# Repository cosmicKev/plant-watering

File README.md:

# Self Watering Plant

To keep your veggies alive that came alive from the [OfferZen] (http://offerzen.com/nl/make) workshop

# Features
  - ESP32 (Wifi / Bluetooth)
  - Flashing is done with a single USB-TypeC
  - Power in:
    - USB at 5V @ 2A max
  - Outputs
    - 2x waterpumps individually with shared power supply of either +5V or +12V
    - 2x USB 5V led strips individually controlled.
  - Sensors:
    - 2x external moisture sensors
    - 1x on board light sensor
    - 1x on board humidity & temperature sesor
    - 1x user custom sensor (till 3.3V

# MCAD - Mechanical CAD
## Pot pipe clips

## Electronics Enclosure

# ECAD - Electronics CAD

# Firmware

# Version

# Authors
Kevin Pinto

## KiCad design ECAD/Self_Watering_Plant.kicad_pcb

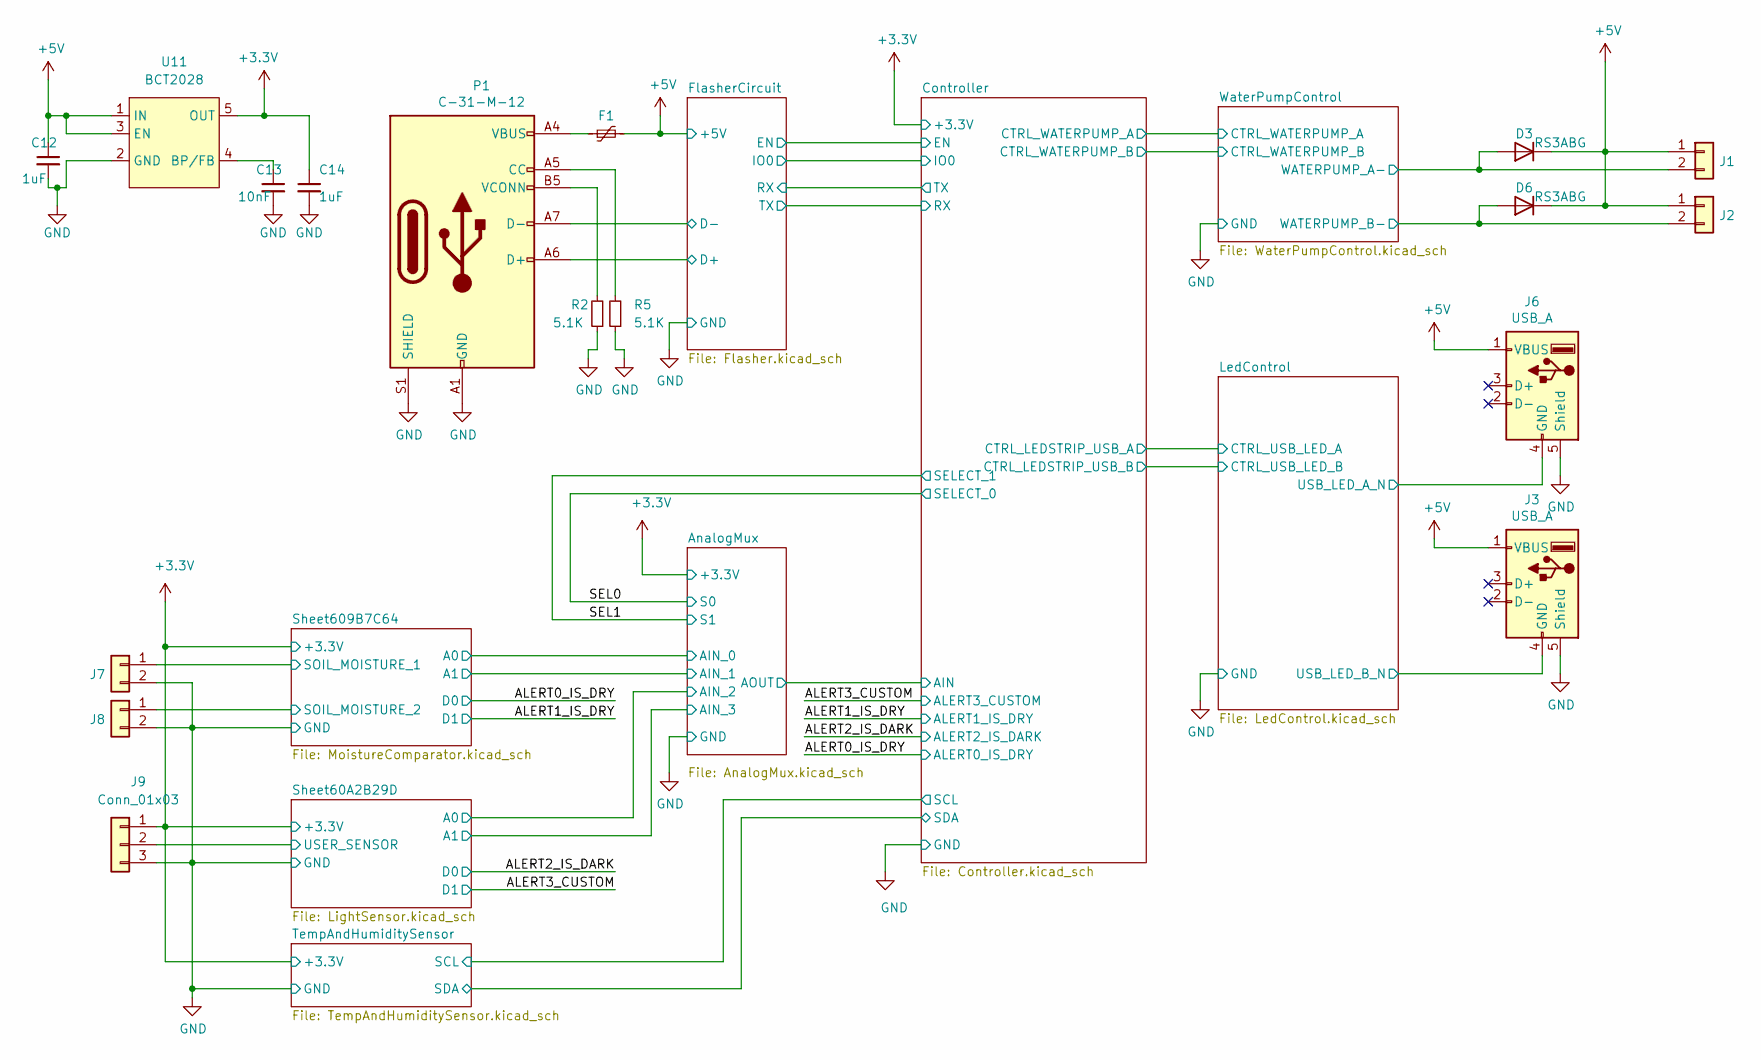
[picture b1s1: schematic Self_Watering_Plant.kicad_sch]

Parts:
C12, C14: 1uF; C_0603_1608Metric
C13: 10nF; C_0603_1608Metric
D3, D6: RS3ABG; D_SMB
F1: Polyfuse_Small; Fuse_1812_4532Metric
J1, J2: Conn_01x02; TB001-500-02BE
J3, J6: USB_A; USB_A_Molex_67643_Horizontal
J7, J8: Conn_01x02; JST_XH_S2B-XH-A_1x02_P2.50mm_Horizontal
J9: Conn_01x03; JST_XH_S3B-XH-A_1x03_P2.50mm_Horizontal
P1: C-31-M-12; USB_C_Receptacle_HRO_TYPE-C-31-M-12
R2, R5: 5.1K; R_0603_1608Metric
U11: BCT2028; SOT-23-5

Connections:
+3V3: C14.1, J9.1, U11.5 (OUT); also elsewhere on the board
+5V: C12.1, D3.1 (K), D6.1 (K), F1.2, J1.1, J2.1, J3.1 (VBUS), J6.1 (VBUS), U11.1 (IN), U11.3 (EN); also elsewhere on the board
/AnalogMux/AIN_0: J8.1; also elsewhere on the board
/AnalogMux/AIN_1: J7.1; also elsewhere on the board
/AnalogMux/AIN_2: J9.2; also elsewhere on the board
/FlasherCircuit/D+: P1.A6 (D+); also elsewhere on the board
/FlasherCircuit/D-: P1.A7 (D-); also elsewhere on the board
/LedControl/USB_LED_A_N: J6.4 (GND); also elsewhere on the board
/LedControl/USB_LED_B_N: J3.4 (GND); also elsewhere on the board
/WaterPumpControl/WATERPUMP_A-: D3.2 (A), J1.2; also elsewhere on the board
/WaterPumpControl/WATERPUMP_B-: D6.2 (A), J2.2; also elsewhere on the board
GND: C12.2, C13.2, C14.2, J3.5 (Shield), J6.5 (Shield), J7.2, J8.2, J9.3, P1.A1 (GND), P1.A12 (GND), P1.B1 (GND), P1.B12 (GND), P1.S1 (SHIELD), R2.1, R5.1, U11.2 (GND); also elsewhere on the board
unnamed: C13.1, U11.4 (BP/FB)
unnamed: F1.1, P1.A4 (VBUS), P1.A9 (VBUS), P1.B4 (VBUS), P1.B9 (VBUS)
unnamed: P1.A5 (CC), R5.2
unnamed: P1.B5 (VCONN), R2.2

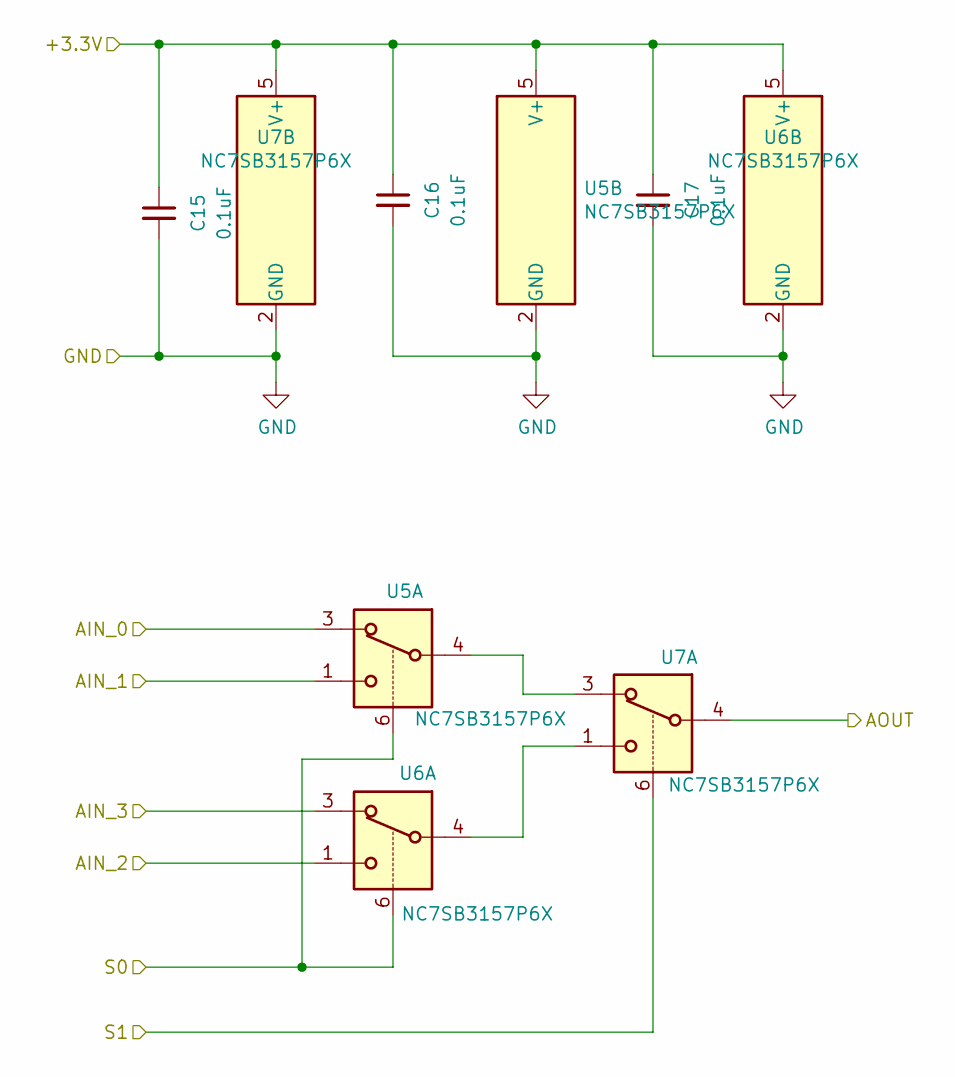
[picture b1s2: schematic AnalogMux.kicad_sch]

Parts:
C15, C16, C17: 0.1uF; C_0603_1608Metric
U5, U6, U7: NC7SB3157P6X; SOT-363_SC-70-6

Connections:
+3V3: C15.1, C16.1, C17.1, U5.5 (V+), U6.5 (V+), U7.5 (V+); also elsewhere on the board
/AnalogMux/AIN_0: U5.3; also elsewhere on the board
/AnalogMux/AIN_1: U5.1; also elsewhere on the board
/AnalogMux/AIN_2: U6.1; also elsewhere on the board
/AnalogMux/AIN_3: U6.3; also elsewhere on the board
/AnalogMux/AOUT: U7.4; also elsewhere on the board
/SEL0: U5.6, U6.6; also elsewhere on the board
/SEL1: U7.6; also elsewhere on the board
GND: C15.2, C16.2, C17.2, U5.2 (GND), U6.2 (GND), U7.2 (GND); also elsewhere on the board
unnamed: U5.4, U7.3
unnamed: U6.4, U7.1

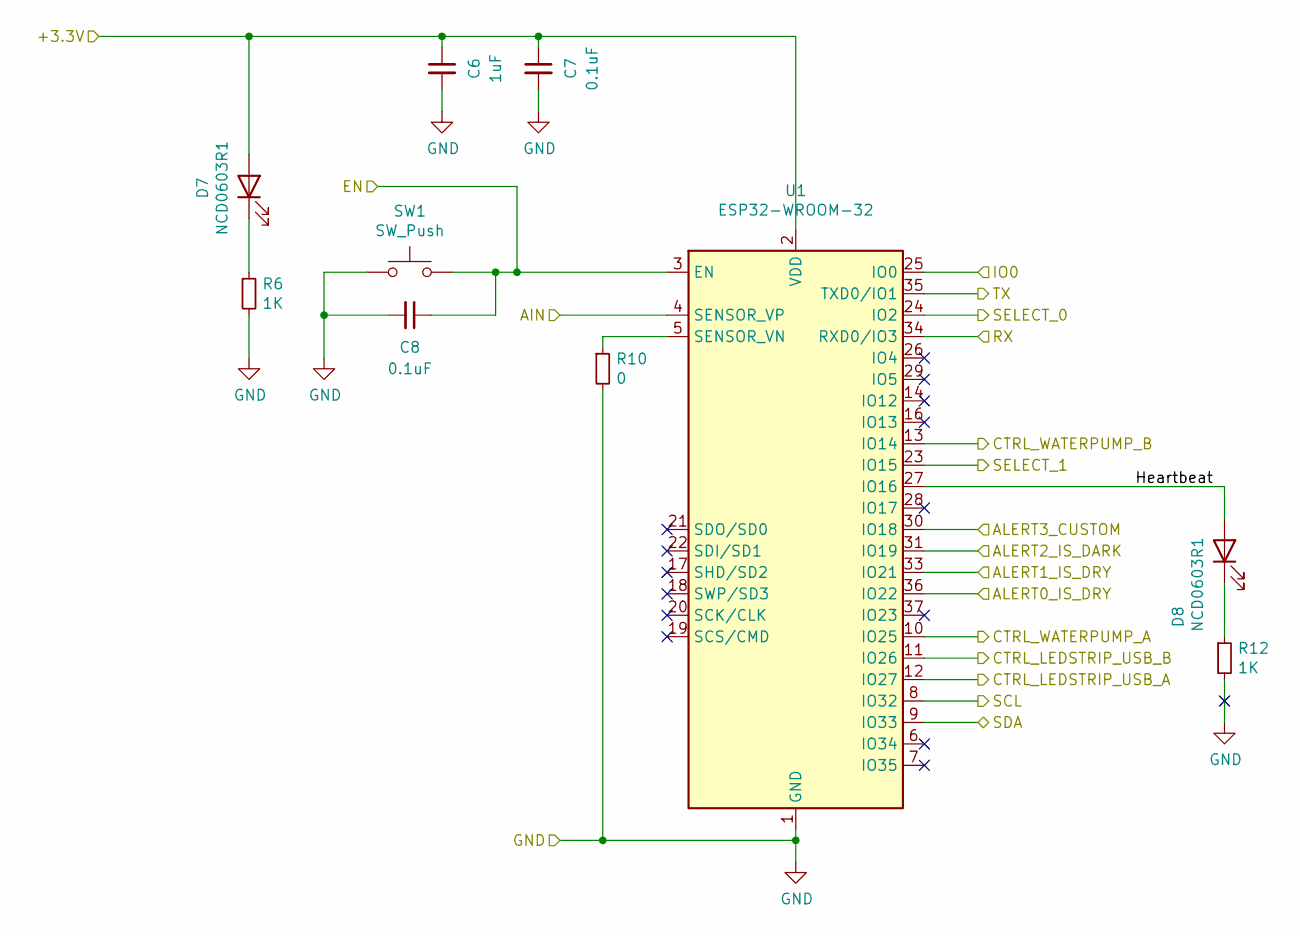
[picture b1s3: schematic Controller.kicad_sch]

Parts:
C6: 1uF; C_0603_1608Metric
C7, C8: 0.1uF; C_0603_1608Metric
D7, D8: NCD0603R1; LED_0603_1608Metric
R6, R12: 1K; R_0603_1608Metric
R10: 0; R_0603_1608Metric
SW1: SW_Push; SW_PUSH_6mm_H4.3mm
U1: ESP32-WROOM-32

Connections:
+3V3: C6.1, C7.1, D7.2 (A), U1.2 (VDD); also elsewhere on the board
/ALERT0_IS_DRY: U1.36 (IO22); also elsewhere on the board
/ALERT1_IS_DRY: U1.33 (IO21); also elsewhere on the board
/ALERT2_IS_DARK: U1.31 (IO19); also elsewhere on the board
/ALERT3_CUSTOM: U1.30 (IO18); also elsewhere on the board
/AnalogMux/AOUT: U1.4 (SENSOR_VP); also elsewhere on the board
/Controller/CTRL_LEDSTRIP_USB_A: U1.12 (IO27); also elsewhere on the board
/Controller/CTRL_LEDSTRIP_USB_B: U1.11 (IO26); also elsewhere on the board
/Controller/CTRL_WATERPUMP_A: U1.10 (IO25); also elsewhere on the board
/Controller/CTRL_WATERPUMP_B: U1.13 (IO14); also elsewhere on the board
/Controller/EN: C8.1, SW1.2, U1.3 (EN); also elsewhere on the board
/Controller/Heartbeat: D8.2 (A), U1.27 (IO16)
/Controller/IO0: U1.25 (IO0); also elsewhere on the board
/Controller/RX: U1.34 (RXD0/IO3); also elsewhere on the board
/Controller/SCL: U1.8 (IO32); also elsewhere on the board
/Controller/SDA: U1.9 (IO33); also elsewhere on the board
/Controller/TX: U1.35 (TXD0/IO1); also elsewhere on the board
/SEL0: U1.24 (IO2); also elsewhere on the board
/SEL1: U1.23 (IO15); also elsewhere on the board
GND: C6.2, C7.2, C8.2, R6.2, R10.2, R12.2, SW1.1, U1.1 (GND), U1.15 (GND), U1.38 (GND), U1.39 (GND); also elsewhere on the board
unnamed: D7.1 (K), R6.1
unnamed: D8.1 (K), R12.1
unnamed: R10.1, U1.5 (SENSOR_VN)

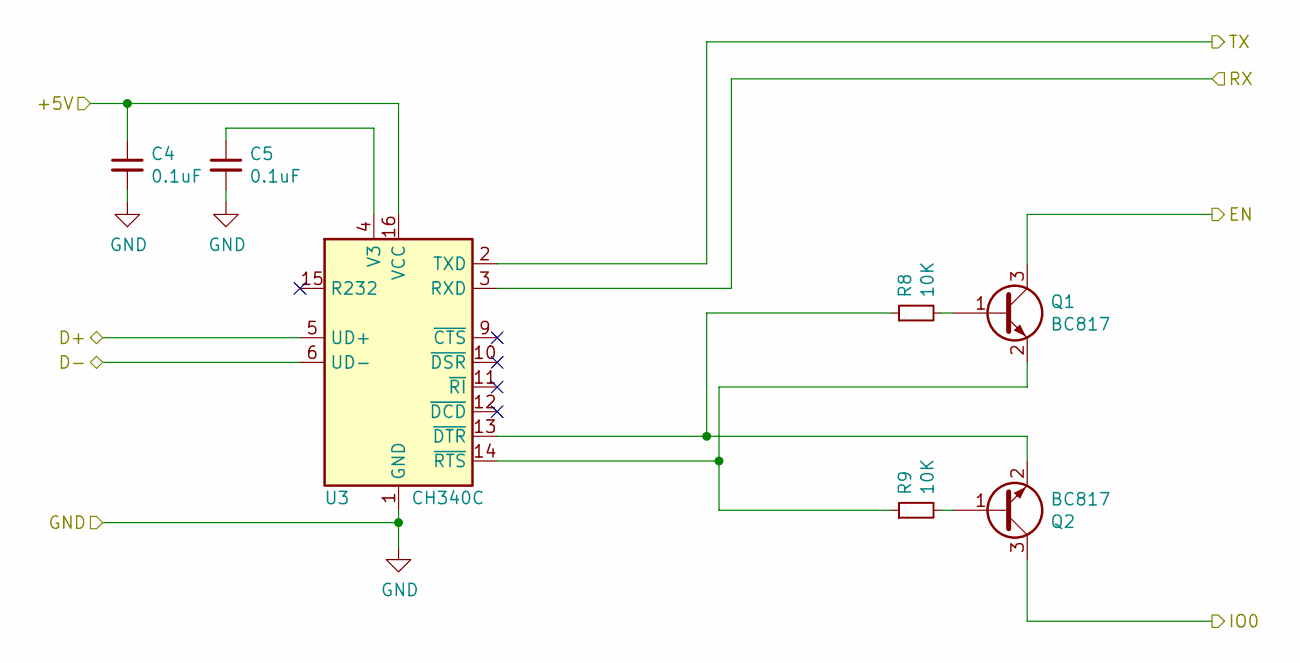
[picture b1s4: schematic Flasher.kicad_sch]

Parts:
C4, C5: 0.1uF; C_0603_1608Metric
Q1, Q2: BC817; SOT-23
R8, R9: 10K; R_0603_1608Metric
U3: CH340C; SOIC-16_3.9x9.9mm_P1.27mm

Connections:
+5V: C4.1, U3.16 (VCC); also elsewhere on the board
/Controller/EN: Q1.3 (C); also elsewhere on the board
/Controller/IO0: Q2.3 (C); also elsewhere on the board
/Controller/RX: U3.2 (TXD); also elsewhere on the board
/Controller/TX: U3.3 (RXD); also elsewhere on the board
/FlasherCircuit/D+: U3.5 (UD+); also elsewhere on the board
/FlasherCircuit/D-: U3.6 (UD-); also elsewhere on the board
GND: C4.2, C5.2, U3.1 (GND); also elsewhere on the board
unnamed: C5.1, U3.4 (V3)
unnamed: Q1.1 (B), R8.2
unnamed: Q1.2 (E), R9.1, U3.14 (~RTS)
unnamed: Q2.1 (B), R9.2
unnamed: Q2.2 (E), R8.1, U3.13 (~DTR)

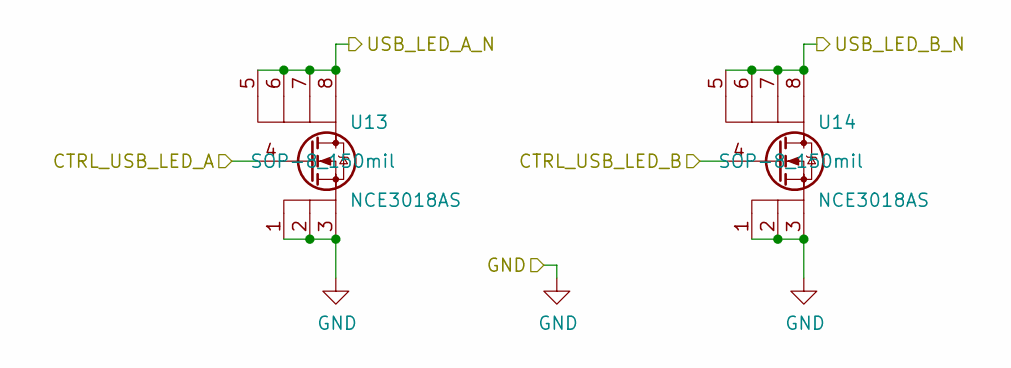
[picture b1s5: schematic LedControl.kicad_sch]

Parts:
U13, U14: NCE3018AS; SO-8_3.9x4.9mm_P1.27mm

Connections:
/Controller/CTRL_LEDSTRIP_USB_A: U13.4; also elsewhere on the board
/Controller/CTRL_LEDSTRIP_USB_B: U14.4; also elsewhere on the board
/LedControl/USB_LED_A_N: U13.5, U13.6, U13.7, U13.8; also elsewhere on the board
/LedControl/USB_LED_B_N: U14.5, U14.6, U14.7, U14.8; also elsewhere on the board
GND: U13.1, U13.2, U13.3, U14.1, U14.2, U14.3; also elsewhere on the board

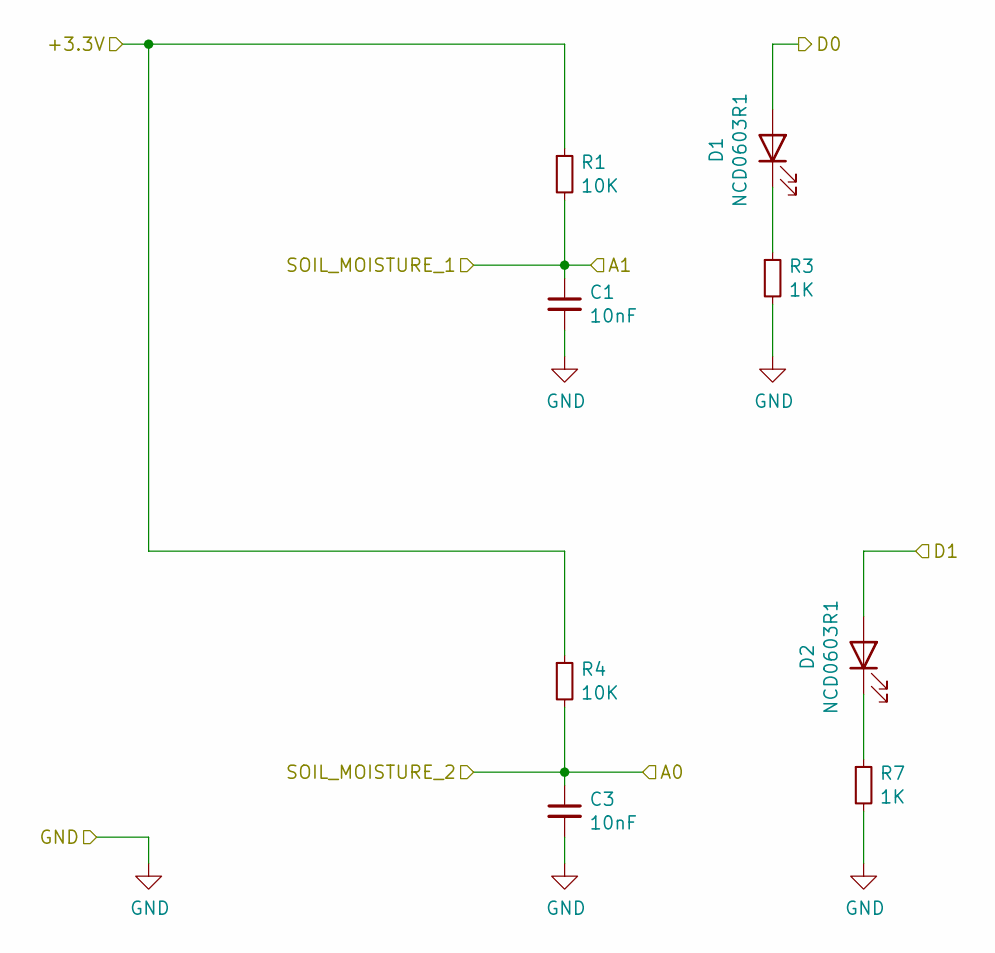
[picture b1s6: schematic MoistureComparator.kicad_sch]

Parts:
C1, C3: 10nF; C_0603_1608Metric
D1, D2: NCD0603R1; LED_0603_1608Metric
R1, R4: 10K; R_0603_1608Metric
R3, R7: 1K; R_0603_1608Metric

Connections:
+3V3: R1.1, R4.1; also elsewhere on the board
/ALERT0_IS_DRY: D1.2 (A); also elsewhere on the board
/ALERT1_IS_DRY: D2.2 (A); also elsewhere on the board
/AnalogMux/AIN_0: C3.1, R4.2; also elsewhere on the board
/AnalogMux/AIN_1: C1.1, R1.2; also elsewhere on the board
GND: C1.2, C3.2, R3.2, R7.2; also elsewhere on the board
unnamed: D1.1 (K), R3.1
unnamed: D2.1 (K), R7.1

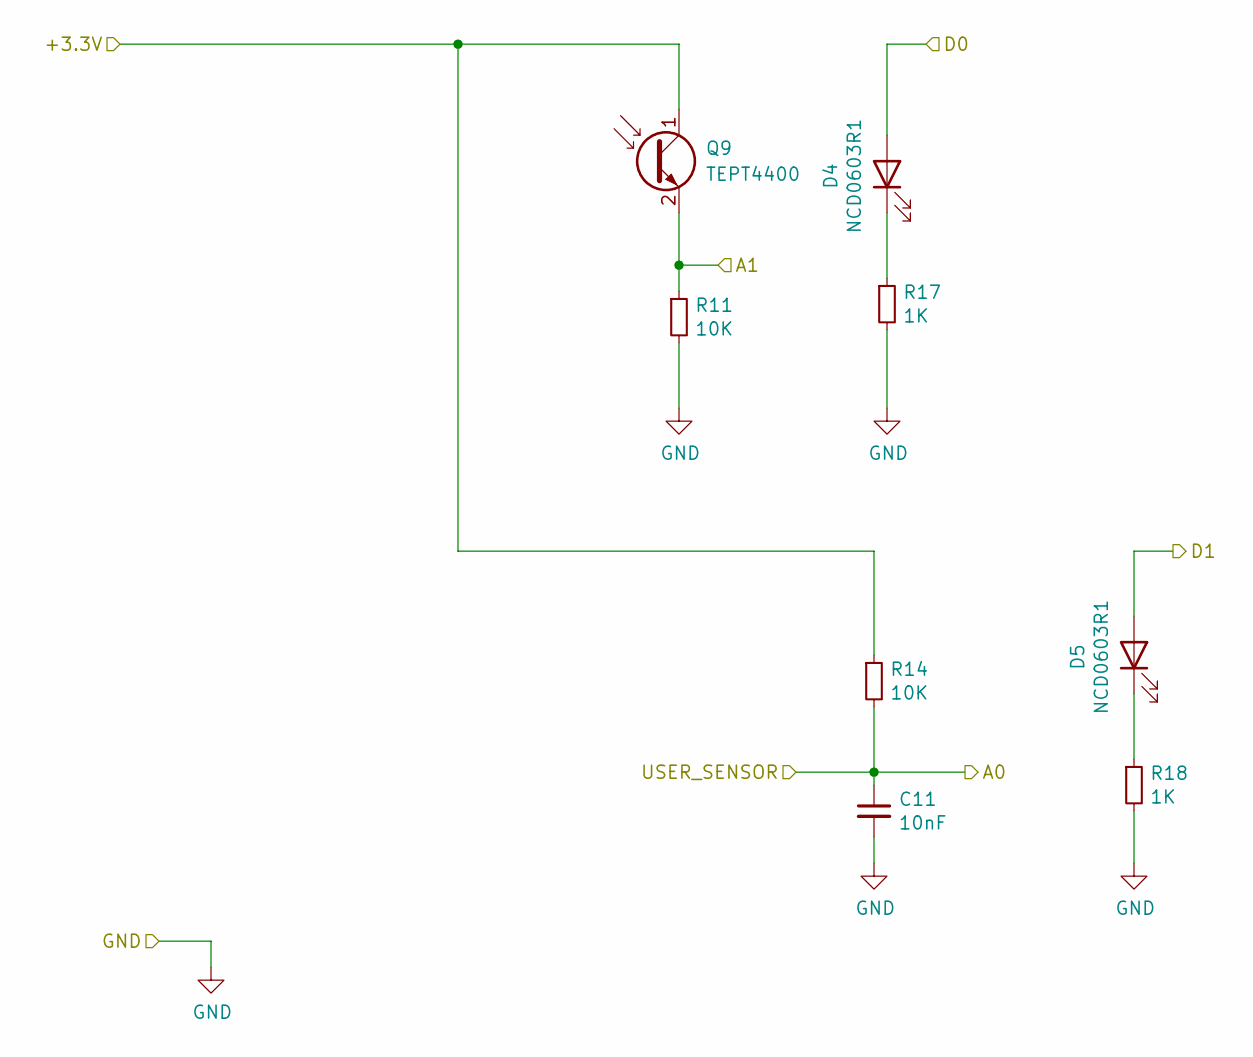
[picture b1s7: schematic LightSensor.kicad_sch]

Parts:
C11: 10nF; C_0603_1608Metric
D4, D5: NCD0603R1; LED_0603_1608Metric
Q9: TEPT4400; LED_D3.0mm_Clear
R11, R14: 10K; R_0603_1608Metric
R17, R18: 1K; R_0603_1608Metric

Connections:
+3V3: Q9.1 (C), R14.1; also elsewhere on the board
/ALERT2_IS_DARK: D4.2 (A); also elsewhere on the board
/ALERT3_CUSTOM: D5.2 (A); also elsewhere on the board
/AnalogMux/AIN_2: C11.1, R14.2; also elsewhere on the board
/AnalogMux/AIN_3: Q9.2 (E), R11.1; also elsewhere on the board
GND: C11.2, R11.2, R17.2, R18.2; also elsewhere on the board
unnamed: D4.1 (K), R17.1
unnamed: D5.1 (K), R18.1

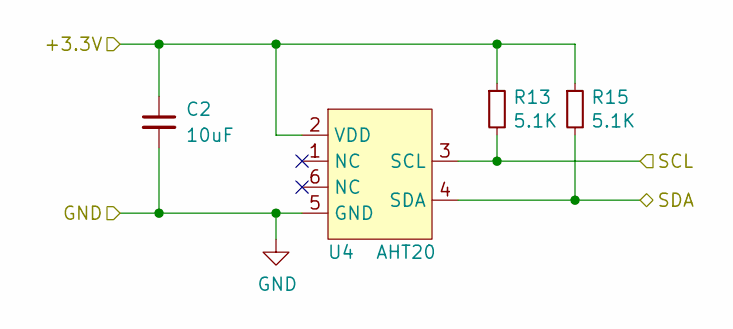
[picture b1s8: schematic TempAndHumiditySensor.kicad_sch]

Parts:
C2: 10uF; C_0603_1608Metric
R13, R15: 5.1K; R_0603_1608Metric
U4: AHT20; SOIC-6

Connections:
+3V3: C2.1, R13.1, R15.1, U4.2 (VDD); also elsewhere on the board
/Controller/SCL: R13.2, U4.3 (SCL); also elsewhere on the board
/Controller/SDA: R15.2, U4.4 (SDA); also elsewhere on the board
GND: C2.2, U4.5 (GND); also elsewhere on the board

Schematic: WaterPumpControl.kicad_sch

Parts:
U2, U9: NCE3018AS; SO-8_3.9x4.9mm_P1.27mm

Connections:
/Controller/CTRL_WATERPUMP_A: U2.4; also elsewhere on the board
/Controller/CTRL_WATERPUMP_B: U9.4; also elsewhere on the board
/WaterPumpControl/WATERPUMP_A-: U2.5, U2.6, U2.7, U2.8; also elsewhere on the board
/WaterPumpControl/WATERPUMP_B-: U9.5, U9.6, U9.7, U9.8; also elsewhere on the board
GND: U2.1, U2.2, U2.3, U9.1, U9.2, U9.3; also elsewhere on the board

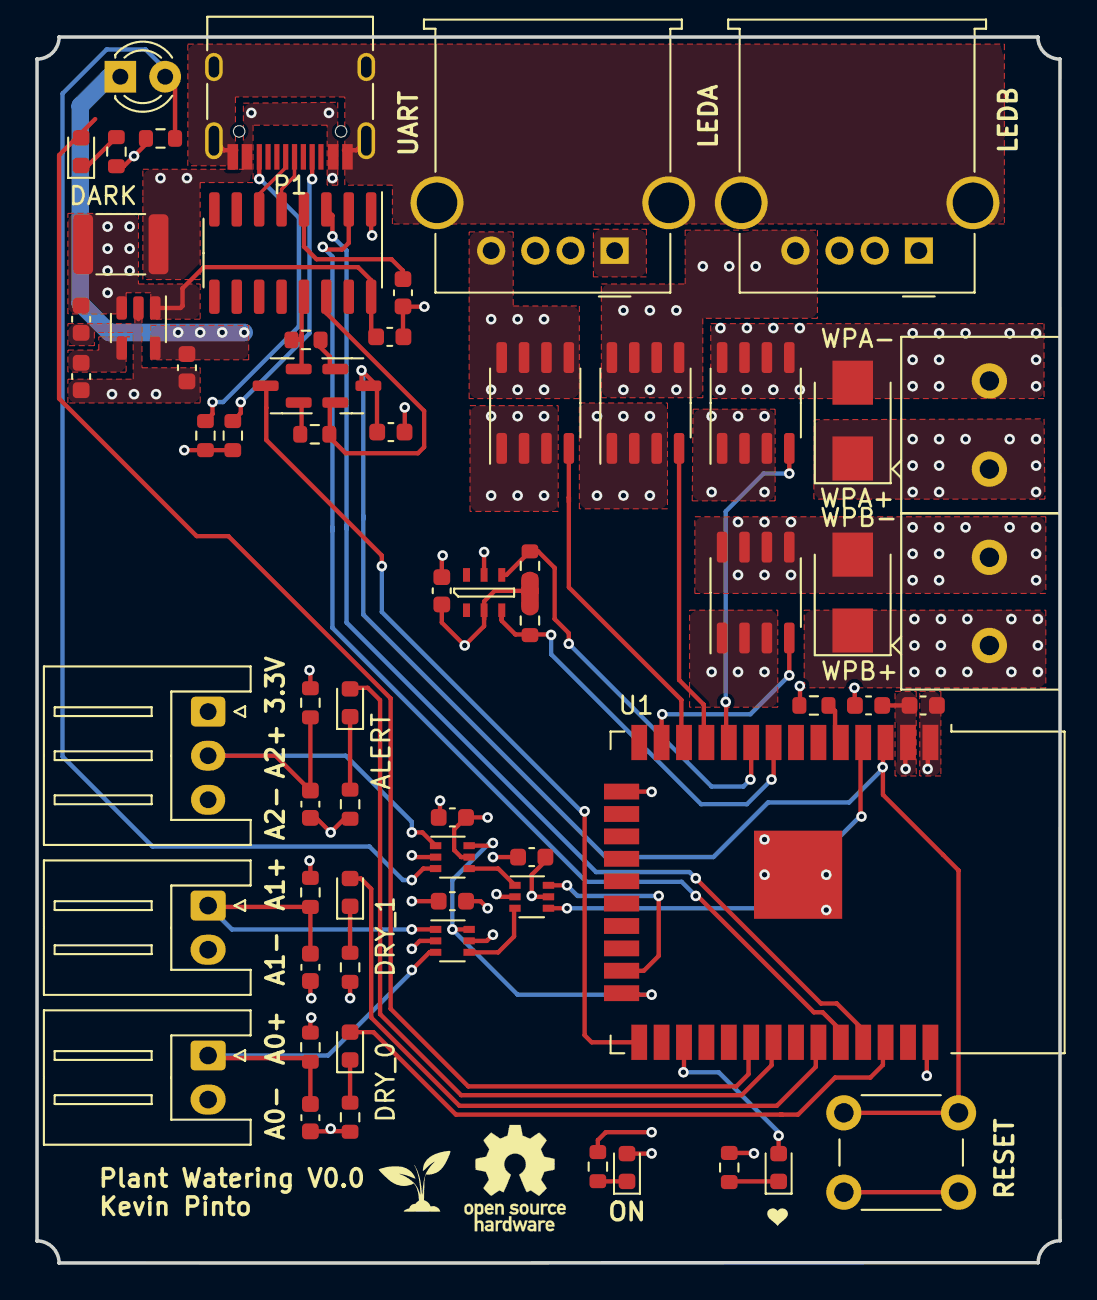
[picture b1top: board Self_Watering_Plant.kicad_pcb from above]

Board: 4 copper layers, 58.0 x 69.5 mm, 64 parts (0 on the bottom side), 49 nets.

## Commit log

2021-05-06 adding 3d printed files of fixtures for the plant pot
2021-05-07 making a small pcb that contains everything we learn from the workshop with sensors and other functionality
2021-05-07 porting project to kicad 5.99, fixing some error in schematics. Getting ready to lay down the layout and order in jlcpcb
2021-05-09 pcb layout has started, still ned to make 5V to 3.3V power supply, add dip switch do individually control input power of each switch, 5V or 12V
2021-05-16 finishing up pcb, only billonly bill of materials need to be done to be compatible with lc from jlcpcb
2021-05-16 BOM fixed, ready to order
2021-05-16 found quite some errors after my review, fixed them before purchase a sample of 5
2021-05-27 first add of all tools for plant-watering firmware
2021-06-16 adding production and step files
2021-11-13 added production files
